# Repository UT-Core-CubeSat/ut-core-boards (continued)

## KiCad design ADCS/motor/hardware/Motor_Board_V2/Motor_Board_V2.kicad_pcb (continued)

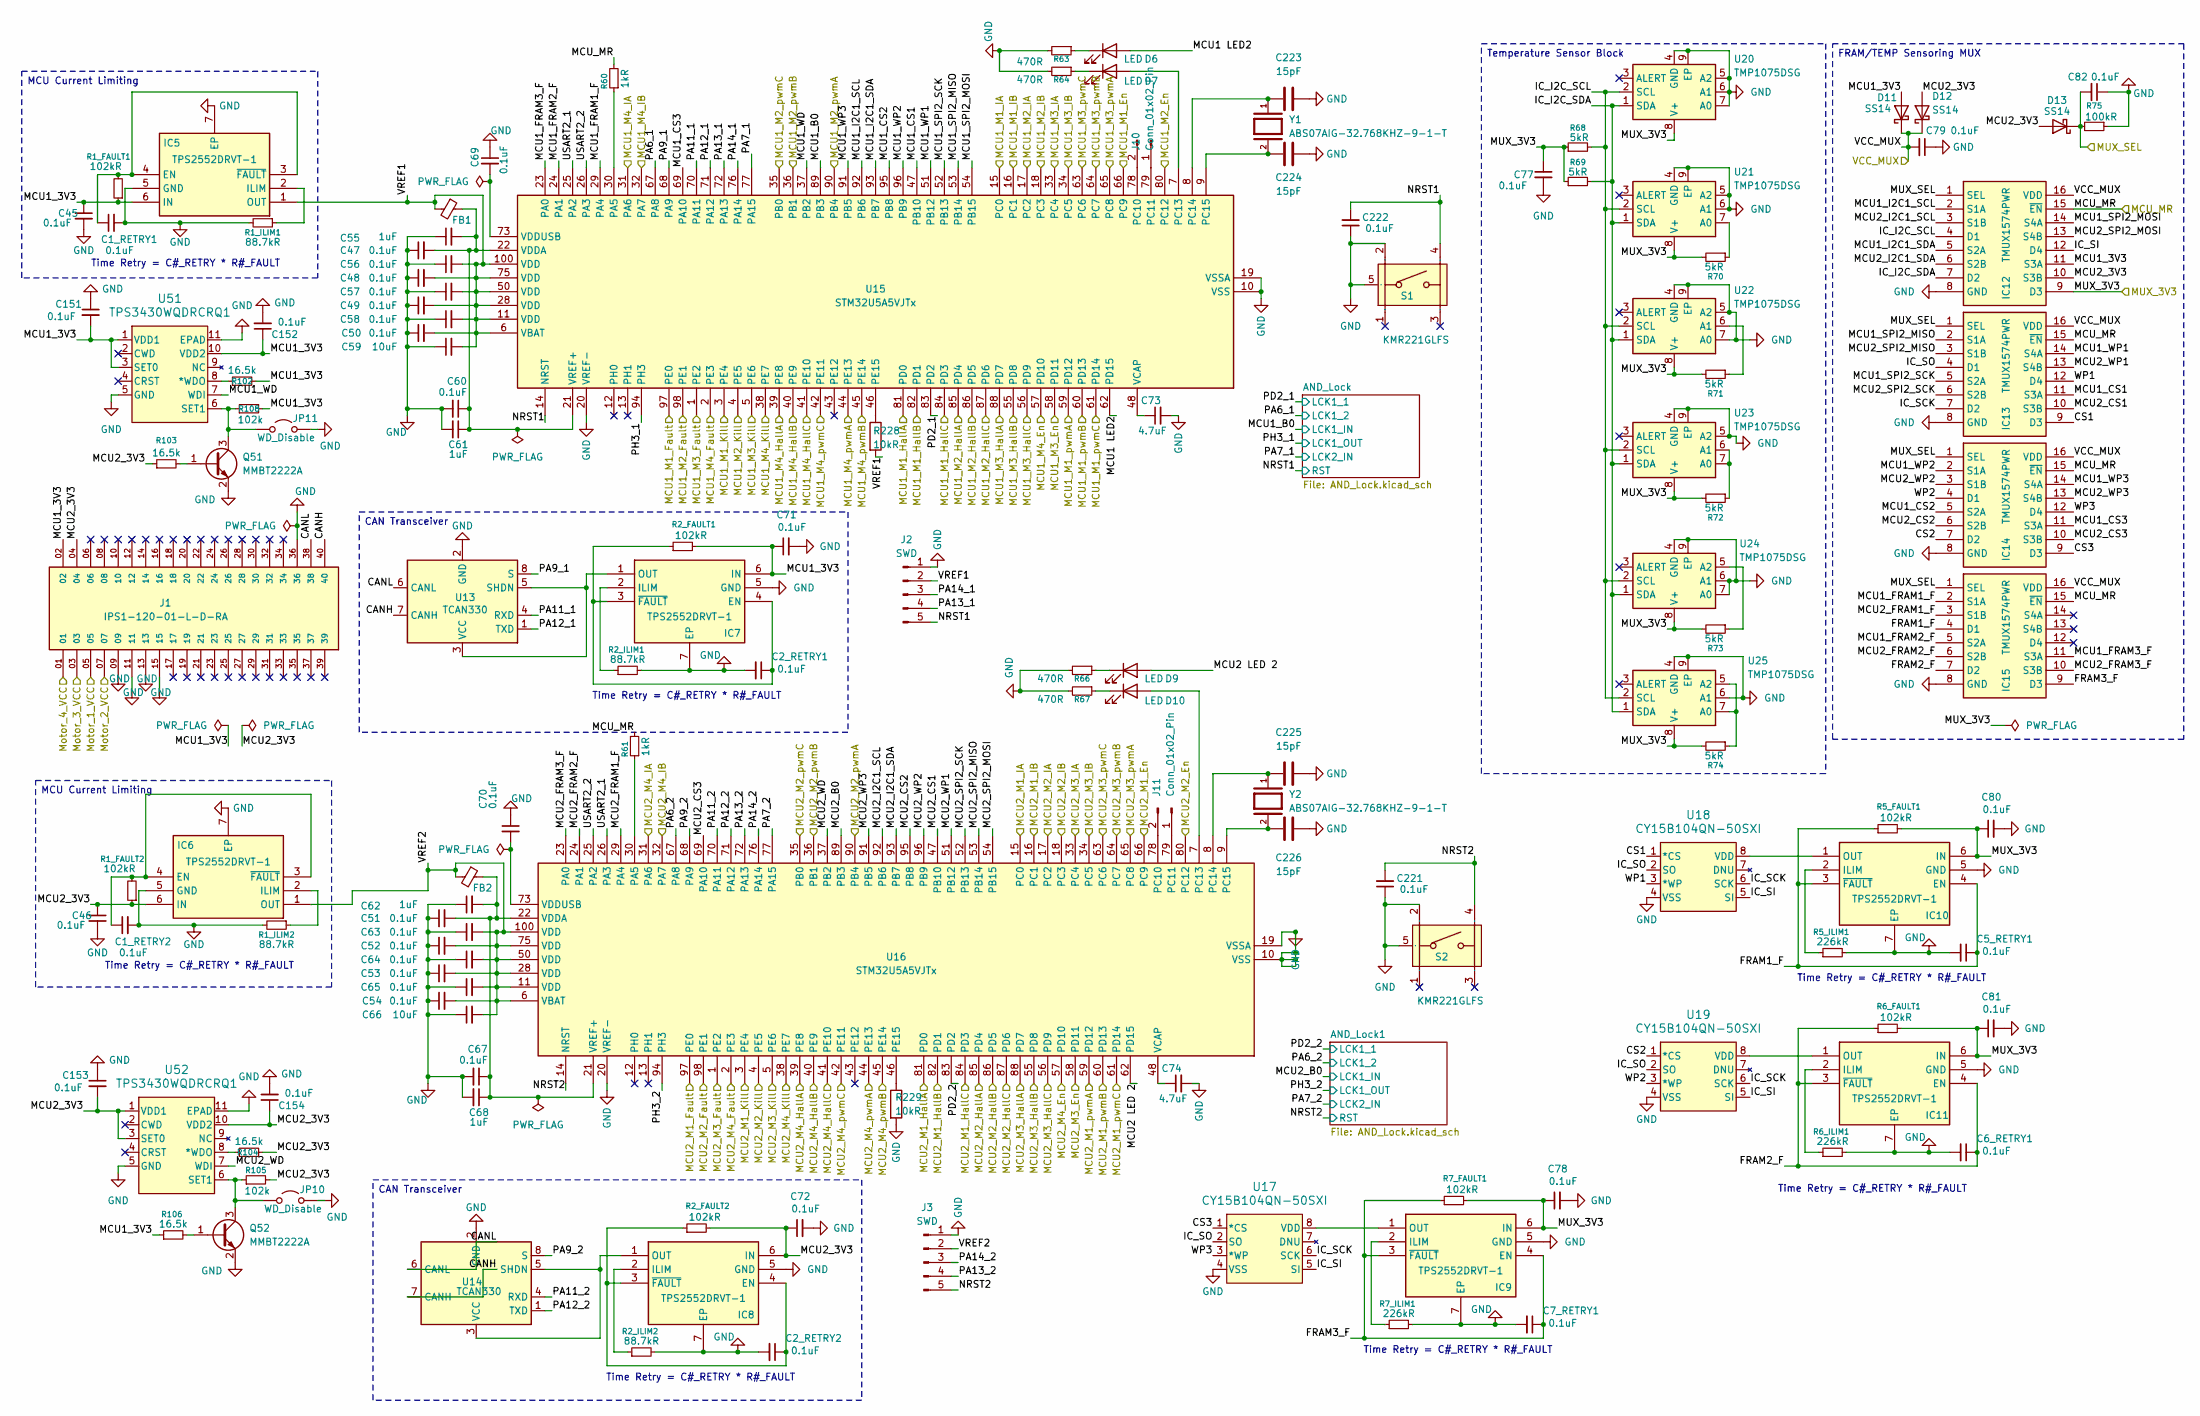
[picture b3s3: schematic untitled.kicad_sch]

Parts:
C1_RETRY1, C1_RETRY2, C2_RETRY1, C2_RETRY2, C5_RETRY1, C6_RETRY1, C7_RETRY1, C45, C46, C47, C48, C49, C50, C51, C52, C53, C54, C56, C57, C58, C63, C64, C65, C69, C70, C71, C72, C77, C78, C79, C80, C81, C82, C151, C152, C153, C154, C221, C222: 0.1uF; C_0603_1608Metric_Pad1.08x0.95mm_HandSolder
C55, C62: 1uF; C_0603_1608Metric_Pad1.08x0.95mm_HandSolder
C59, C66: 10uF; C_0603_1608Metric_Pad1.08x0.95mm_HandSolder
C60, C67: 0.1uF; C_0805_2012Metric_Pad1.18x1.45mm_HandSolder
C61, C68: 1uF; C_0805_2012Metric_Pad1.18x1.45mm_HandSolder
C73, C74: 4.7uF; C_0805_2012Metric_Pad1.18x1.45mm_HandSolder
C223, C224, C225, C226: 15pF; C_0603_1608Metric
D6, D7, D9, D10: LED; LED_0201_0603Metric_Pad0.64x0.40mm_HandSolder
D11, D12, D13: SS14; D_SMA
FB1, FB2: FerriteBead_Small; R_0805_2012Metric_Pad1.20x1.40mm_HandSolder
IC5, IC6, IC7, IC8, IC9, IC10, IC11: TPS2552DRVT-1; Mouser Part Number 595-TPS2552DRVT-1
IC12, IC13, IC14, IC15: TMUX1574PWR; Mouser Part Number 595-TMUX1574PWR
J1: IPS1-120-01-L-D-RA
J2, J3: SWD; PinHeader_1x05_P2.54mm_Vertical
J10, J11: Conn_01x02_Pin; PinHeader_1x02_P2.54mm_Vertical
JP10, JP11: WD_Disable; TestPoint_2Pads_Pitch2.54mm_Drill0.8mm
Q51, Q52: MMBT2222A; SOT-23
R1_FAULT1, R1_FAULT2, R2_FAULT1, R2_FAULT2, R5_FAULT1, R6_FAULT1, R7_FAULT1: 102kR; R_0805_2012Metric_Pad1.20x1.40mm_HandSolder
R1_ILIM1, R1_ILIM2, R2_ILIM1, R2_ILIM2: 88.7kR; R_0805_2012Metric_Pad1.20x1.40mm_HandSolder
R5_ILIM1, R6_ILIM1, R7_ILIM1: 226kR; R_0805_2012Metric_Pad1.20x1.40mm_HandSolder
R60, R61: 1kR; R_0805_2012Metric_Pad1.20x1.40mm_HandSolder
R63, R64, R66, R67: 470R; R_0805_2012Metric_Pad1.20x1.40mm_HandSolder
R68, R69, R70, R71, R72, R73, R74: 5kR; R_0603_1608Metric_Pad0.98x0.95mm_HandSolder
R75: 100kR; R_0805_2012Metric_Pad1.20x1.40mm_HandSolder
R102, R103, R104, R106: 16.5k; R_0805_2012Metric_Pad1.20x1.40mm_HandSolder
R105, R108: 102k; R_0805_2012Metric_Pad1.20x1.40mm_HandSolder
R228, R229: 10kR; R_0805_2012Metric
S1, S2: KMR221GLFS; SW_KMR221GLFS; Manufacturer Part KMR221GLFS; LCSC Part Name 4.6*2.8*1.9mm 立贴 轻触开关
U13, U14: TCAN330; SOIC-8_3.9x4.9mm_P1.27mm
U15, U16: STM32U5A5VJTx; LQFP-100_14x14mm_P0.5mm
U17, U18, U19: CY15B104QN-50SXI
U20, U21, U22, U23, U24, U25: TMP1075DSG; WSON-8-1EP_2x2mm_P0.5mm_EP0.9x1.6mm
U51, U52: TPS3430WQDRCRQ1; SON50P300X300X100-11N
Y1, Y2: ABS07AIG-32.768KHZ-9-1-T; XTAL_ABS07AIG-32.768KHZ-9-1-T; PARTREV 6/7/2022

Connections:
/MUX_3V3: C77.1, C78.1, C80.1, C81.1, IC9.6 (IN), IC10.6 (IN), IC11.6 (IN), IC12.9 (D3), R5_FAULT1.2, R6_FAULT1.2, R7_FAULT1.2, R68.1, R69.1, R70.2, R71.2, R72.2, R73.2, R74.2, U20.8 (V+), U21.8 (V+), U22.8 (V+), U23.8 (V+), U24.8 (V+), U25.8 (V+); also elsewhere on the board
/Motor_1_VCC: J1.05; also elsewhere on the board
/Motor_2_VCC: J1.07; also elsewhere on the board
/Motor_3_VCC: J1.03; also elsewhere on the board
/Motor_4_VCC: J1.01; also elsewhere on the board
/mux/MCU block/CANH: J1.40, U13.7 (CANH), U14.7 (CANH)
/mux/MCU block/CANL: J1.38, U13.6 (CANL), U14.6 (CANL)
/mux/MCU block/CS1: IC13.9 (D3), U18.1 (*CS)
/mux/MCU block/CS2: IC14.7 (D2), U19.1 (*CS)
/mux/MCU block/CS3: IC14.9 (D3), U17.1 (*CS)
/mux/MCU block/FRAM1_F: C5_RETRY1.1, IC10.3 (~FAULT), IC10.4 (EN), IC15.4 (D1), R5_FAULT1.1
/mux/MCU block/FRAM2_F: C6_RETRY1.1, IC11.3 (~FAULT), IC11.4 (EN), IC15.7 (D2), R6_FAULT1.1
/mux/MCU block/FRAM3_F: C7_RETRY1.1, IC9.3 (~FAULT), IC9.4 (EN), IC15.9 (D3), R7_FAULT1.1
/mux/MCU block/IC_I2C_SCL: IC12.4 (D1), R68.2, U20.2 (SCL), U21.2 (SCL), U22.2 (SCL), U23.2 (SCL), U24.2 (SCL), U25.2 (SCL)
/mux/MCU block/IC_I2C_SDA: IC12.7 (D2), R69.2, U20.1 (SDA), U21.1 (SDA), U22.1 (SDA), U23.1 (SDA), U24.1 (SDA), U25.1 (SDA)
/mux/MCU block/IC_SCK: IC13.7 (D2), U17.6 (SCK), U18.6 (SCK), U19.6 (SCK)
/mux/MCU block/IC_SI: IC12.12 (D4), U17.5 (SI), U18.5 (SI), U19.5 (SI)
/mux/MCU block/IC_SO: IC13.4 (D1), U17.2 (SO), U18.2 (SO), U19.2 (SO)
/mux/MCU block/MCU1 LED2: D6.2 (A), U15.62 (PD15)
/mux/MCU block/MCU1_3V3: C45.1, C71.1, C151.2, C152.1, D11.2 (A), IC5.6 (IN), IC7.6 (IN), IC12.11 (S3A), J1.02, R1_FAULT1.1, R2_FAULT1.2, R102.2, R106.1, R108.2, U51.1 (VDD1), U51.3 (SET0), U51.10 (VDD2); also elsewhere on the board
/mux/MCU block/MCU1_B0: U15.89 (PB3); also elsewhere on the board
/mux/MCU block/MCU1_CS1: IC13.11 (S3A), U15.47 (PB10)
/mux/MCU block/MCU1_CS2: IC14.5 (S2A), U15.95 (PB8)
/mux/MCU block/MCU1_CS3: IC14.11 (S3A), U15.69 (PA10)
/mux/MCU block/MCU1_FRAM1_F: IC15.2 (S1A), U15.29 (PA4)
/mux/MCU block/MCU1_FRAM2_F: IC15.5 (S2A), U15.24 (PA1)
/mux/MCU block/MCU1_FRAM3_F: IC15.11 (S3A), U15.23 (PA0)
/mux/MCU block/MCU1_I2C1_SCL: IC12.2 (S1A), U15.92 (PB6)
/mux/MCU block/MCU1_I2C1_SDA: IC12.5 (S2A), U15.93 (PB7)
/mux/MCU block/MCU1_M1_En: U15.66 (PC9); also elsewhere on the board
/mux/MCU block/MCU1_M1_Fault: U15.97 (PE0); also elsewhere on the board
/mux/MCU block/MCU1_M1_HallA: U15.81 (PD0); also elsewhere on the board
/mux/MCU block/MCU1_M1_HallB: U15.82 (PD1); also elsewhere on the board
/mux/MCU block/MCU1_M1_HallC: U15.84 (PD3); also elsewhere on the board
/mux/MCU block/MCU1_M1_IA: U15.15 (PC0); also elsewhere on the board
/mux/MCU block/MCU1_M1_IB: U15.16 (PC1); also elsewhere on the board
/mux/MCU block/MCU1_M1_Kill: U15.3 (PE4); also elsewhere on the board
/mux/MCU block/MCU1_M1_pwmA: U15.59 (PD12); also elsewhere on the board
/mux/MCU block/MCU1_M1_pwmB: U15.60 (PD13); also elsewhere on the board
/mux/MCU block/MCU1_M1_pwmC: U15.61 (PD14); also elsewhere on the board
/mux/MCU block/MCU1_M2_En: U15.80 (PC12); also elsewhere on the board
/mux/MCU block/MCU1_M2_Fault: U15.98 (PE1); also elsewhere on the board
/mux/MCU block/MCU1_M2_HallA: U15.85 (PD4); also elsewhere on the board
/mux/MCU block/MCU1_M2_HallB: U15.86 (PD5); also elsewhere on the board
/mux/MCU block/MCU1_M2_HallC: U15.87 (PD6); also elsewhere on the board
/mux/MCU block/MCU1_M2_IA: U15.17 (PC2); also elsewhere on the board
/mux/MCU block/MCU1_M2_IB: U15.18 (PC3); also elsewhere on the board
/mux/MCU block/MCU1_M2_Kill: U15.4 (PE5); also elsewhere on the board
/mux/MCU block/MCU1_M2_pwmA: U15.90 (PB4); also elsewhere on the board
/mux/MCU block/MCU1_M2_pwmB: U15.36 (PB1); also elsewhere on the board
/mux/MCU block/MCU1_M2_pwmC: U15.35 (PB0); also elsewhere on the board
/mux/MCU block/MCU1_M3_En: U15.58 (PD11); also elsewhere on the board
/mux/MCU block/MCU1_M3_Fault: U15.1 (PE2); also elsewhere on the board
/mux/MCU block/MCU1_M3_HallA: U15.88 (PD7); also elsewhere on the board
/mux/MCU block/MCU1_M3_HallB: U15.55 (PD8); also elsewhere on the board
/mux/MCU block/MCU1_M3_HallC: U15.56 (PD9); also elsewhere on the board
/mux/MCU block/MCU1_M3_IA: U15.33 (PC4); also elsewhere on the board
/mux/MCU block/MCU1_M3_IB: U15.34 (PC5); also elsewhere on the board
/mux/MCU block/MCU1_M3_Kill: U15.5 (PE6); also elsewhere on the board
/mux/MCU block/MCU1_M3_pwmA: U15.65 (PC8); also elsewhere on the board
/mux/MCU block/MCU1_M3_pwmB: U15.64 (PC7); also elsewhere on the board
/mux/MCU block/MCU1_M3_pwmC: U15.63 (PC6); also elsewhere on the board
/mux/MCU block/MCU1_M4_En: U15.57 (PD10); also elsewhere on the board
/mux/MCU block/MCU1_M4_Fault: U15.2 (PE3); also elsewhere on the board
/mux/MCU block/MCU1_M4_HallA: U15.39 (PE8); also elsewhere on the board
/mux/MCU block/MCU1_M4_HallB: U15.40 (PE9); also elsewhere on the board
/mux/MCU block/MCU1_M4_HallC: U15.41 (PE10); also elsewhere on the board
/mux/MCU block/MCU1_M4_IA: U15.31 (PA6); also elsewhere on the board
/mux/MCU block/MCU1_M4_IB: U15.32 (PA7); also elsewhere on the board
/mux/MCU block/MCU1_M4_Kill: U15.38 (PE7); also elsewhere on the board
/mux/MCU block/MCU1_M4_pwmA: U15.44 (PE13); also elsewhere on the board
/mux/MCU block/MCU1_M4_pwmB: U15.45 (PE14); also elsewhere on the board
/mux/MCU block/MCU1_M4_pwmC: U15.42 (PE11); also elsewhere on the board
/mux/MCU block/MCU1_SPI2_MISO: IC13.2 (S1A), U15.53 (PB14)
/mux/MCU block/MCU1_SPI2_MOSI: IC12.14 (S4A), U15.54 (PB15)
/mux/MCU block/MCU1_SPI2_SCK: IC13.5 (S2A), U15.52 (PB13)
/mux/MCU block/MCU1_WD: U15.37 (PB2), U51.7 (WDI)
/mux/MCU block/MCU1_WP1: IC13.14 (S4A), U15.51 (PB12)
/mux/MCU block/MCU1_WP2: IC14.2 (S1A), U15.96 (PB9)
/mux/MCU block/MCU1_WP3: IC14.14 (S4A), U15.91 (PB5)
/mux/MCU block/MCU2 LED 2: D9.2 (A), U16.62 (PD15)
/mux/MCU block/MCU2_3V3: C46.1, C72.1, C153.2, C154.1, D12.2 (A), D13.2 (A), IC6.6 (IN), IC8.6 (IN), IC12.10 (S3B), J1.04, R1_FAULT2.1, R2_FAULT2.2, R103.1, R104.2, R105.2, U52.1 (VDD1), U52.3 (SET0), U52.10 (VDD2); also elsewhere on the board
/mux/MCU block/MCU2_B0: U16.89 (PB3); also elsewhere on the board
/mux/MCU block/MCU2_CS1: IC13.10 (S3B), U16.47 (PB10)
/mux/MCU block/MCU2_CS2: IC14.6 (S2B), U16.95 (PB8)
/mux/MCU block/MCU2_CS3: IC14.10 (S3B), U16.69 (PA10)
/mux/MCU block/MCU2_FRAM1_F: IC15.3 (S1B), U16.29 (PA4)
/mux/MCU block/MCU2_FRAM2_F: IC15.6 (S2B), U16.24 (PA1)
/mux/MCU block/MCU2_FRAM3_F: IC15.10 (S3B), U16.23 (PA0)
/mux/MCU block/MCU2_I2C1_SCL: IC12.3 (S1B), U16.92 (PB6)
/mux/MCU block/MCU2_I2C1_SDA: IC12.6 (S2B), U16.93 (PB7)
/mux/MCU block/MCU2_M1_En: U16.66 (PC9); also elsewhere on the board
/mux/MCU block/MCU2_M1_Fault: U16.97 (PE0); also elsewhere on the board
/mux/MCU block/MCU2_M1_HallA: U16.81 (PD0); also elsewhere on the board
/mux/MCU block/MCU2_M1_HallB: U16.82 (PD1); also elsewhere on the board
/mux/MCU block/MCU2_M1_HallC: U16.84 (PD3); also elsewhere on the board
/mux/MCU block/MCU2_M1_IA: U16.15 (PC0); also elsewhere on the board
/mux/MCU block/MCU2_M1_IB: U16.16 (PC1); also elsewhere on the board
/mux/MCU block/MCU2_M1_Kill: U16.3 (PE4); also elsewhere on the board
/mux/MCU block/MCU2_M1_pwmA: U16.59 (PD12); also elsewhere on the board
/mux/MCU block/MCU2_M1_pwmB: U16.60 (PD13); also elsewhere on the board
/mux/MCU block/MCU2_M1_pwmC: U16.61 (PD14); also elsewhere on the board
/mux/MCU block/MCU2_M2_En: U16.80 (PC12); also elsewhere on the board
/mux/MCU block/MCU2_M2_Fault: U16.98 (PE1); also elsewhere on the board
/mux/MCU block/MCU2_M2_HallA: U16.85 (PD4); also elsewhere on the board
/mux/MCU block/MCU2_M2_HallB: U16.86 (PD5); also elsewhere on the board
/mux/MCU block/MCU2_M2_HallC: U16.87 (PD6); also elsewhere on the board
/mux/MCU block/MCU2_M2_IA: U16.17 (PC2); also elsewhere on the board
/mux/MCU block/MCU2_M2_IB: U16.18 (PC3); also elsewhere on the board
/mux/MCU block/MCU2_M2_Kill: U16.4 (PE5); also elsewhere on the board
/mux/MCU block/MCU2_M2_pwmA: U16.90 (PB4); also elsewhere on the board
/mux/MCU block/MCU2_M2_pwmB: U16.36 (PB1); also elsewhere on the board
/mux/MCU block/MCU2_M2_pwmC: U16.35 (PB0); also elsewhere on the board
/mux/MCU block/MCU2_M3_En: U16.58 (PD11); also elsewhere on the board
/mux/MCU block/MCU2_M3_Fault: U16.1 (PE2); also elsewhere on the board
/mux/MCU block/MCU2_M3_HallA: U16.88 (PD7); also elsewhere on the board
/mux/MCU block/MCU2_M3_HallB: U16.55 (PD8); also elsewhere on the board
/mux/MCU block/MCU2_M3_HallC: U16.56 (PD9); also elsewhere on the board
/mux/MCU block/MCU2_M3_IA: U16.33 (PC4); also elsewhere on the board
/mux/MCU block/MCU2_M3_IB: U16.34 (PC5); also elsewhere on the board
/mux/MCU block/MCU2_M3_Kill: U16.5 (PE6); also elsewhere on the board
/mux/MCU block/MCU2_M3_pwmA: U16.65 (PC8); also elsewhere on the board
/mux/MCU block/MCU2_M3_pwmB: U16.64 (PC7); also elsewhere on the board
/mux/MCU block/MCU2_M3_pwmC: U16.63 (PC6); also elsewhere on the board
/mux/MCU block/MCU2_M4_En: U16.57 (PD10); also elsewhere on the board
/mux/MCU block/MCU2_M4_Fault: U16.2 (PE3); also elsewhere on the board
/mux/MCU block/MCU2_M4_HallA: U16.39 (PE8); also elsewhere on the board
/mux/MCU block/MCU2_M4_HallB: U16.40 (PE9); also elsewhere on the board
/mux/MCU block/MCU2_M4_HallC: U16.41 (PE10); also elsewhere on the board
/mux/MCU block/MCU2_M4_IA: U16.31 (PA6); also elsewhere on the board
/mux/MCU block/MCU2_M4_IB: U16.32 (PA7); also elsewhere on the board
/mux/MCU block/MCU2_M4_Kill: U16.38 (PE7); also elsewhere on the board
/mux/MCU block/MCU2_M4_pwmA: U16.44 (PE13); also elsewhere on the board
/mux/MCU block/MCU2_M4_pwmB: U16.45 (PE14); also elsewhere on the board
/mux/MCU block/MCU2_M4_pwmC: U16.42 (PE11); also elsewhere on the board
/mux/MCU block/MCU2_SPI2_MISO: IC13.3 (S1B), U16.53 (PB14)
/mux/MCU block/MCU2_SPI2_MOSI: IC12.13 (S4B), U16.54 (PB15)
/mux/MCU block/MCU2_SPI2_SCK: IC13.6 (S2B), U16.52 (PB13)
/mux/MCU block/MCU2_WD: U16.37 (PB2), U52.7 (WDI)
/mux/MCU block/MCU2_WP1: IC13.13 (S4B), U16.51 (PB12)
/mux/MCU block/MCU2_WP2: IC14.3 (S1B), U16.96 (PB9)
/mux/MCU block/MCU2_WP3: IC14.13 (S4B), U16.91 (PB5)
/mux/MCU block/PA6_1: U15.67 (PA8); also elsewhere on the board
/mux/MCU block/PA6_2: U16.67 (PA8); also elsewhere on the board
/mux/MCU block/PA7_1: U15.77 (PA15); also elsewhere on the board
/mux/MCU block/PA7_2: U16.77 (PA15); also elsewhere on the board
/mux/MCU block/PA9_1: U13.8 (S), U15.68 (PA9)
/mux/MCU block/PA9_2: U14.8 (S), U16.68 (PA9)
/mux/MCU block/PA11_1: U13.4 (RXD), U15.70 (PA11)
/mux/MCU block/PA11_2: U14.4 (RXD), U16.70 (PA11)
/mux/MCU block/PA12_1: U13.1 (TXD), U15.71 (PA12)
/mux/MCU block/PA12_2: U14.1 (TXD), U16.71 (PA12)
/mux/MCU block/PA13_1: J2.4, U15.72 (PA13)
/mux/MCU block/PA13_2: J3.4, U16.72 (PA13)
/mux/MCU block/PA14_1: J2.3, U15.76 (PA14)
/mux/MCU block/PA14_2: J3.3, U16.76 (PA14)
/mux/MCU block/PD2_1: U15.83 (PD2); also elsewhere on the board
/mux/MCU block/PD2_2: U16.83 (PD2); also elsewhere on the board
/mux/MCU block/PH3_1: U15.94 (PH3); also elsewhere on the board
/mux/MCU block/PH3_2: U16.94 (PH3); also elsewhere on the board
/mux/MCU block/USART2_1: U15.25 (PA2), U16.26 (PA3)
/mux/MCU block/USART2_2: U15.26 (PA3), U16.25 (PA2)
/mux/MCU block/VREF1: C48.2, C49.2, C50.2, C56.2, C57.2, C58.2, C59.2, FB1.2, IC5.1 (OUT), J2.2, R228.2, U15.6 (VBAT), U15.11 (VDD), U15.28 (VDD), U15.50 (VDD), U15.75 (VDD), U15.100 (VDD)
/mux/MCU block/VREF2: C52.2, C53.2, C54.2, C63.2, C64.2, C65.2, C66.2, FB2.2, IC6.1 (OUT), J3.2, U16.6 (VBAT), U16.11 (VDD), U16.28 (VDD), U16.50 (VDD), U16.75 (VDD), U16.100 (VDD)
/mux/MCU block/WP1: IC13.12 (D4), U18.3 (*WP)
/mux/MCU block/WP2: IC14.4 (D1), U19.3 (*WP)
/mux/MCU block/WP3: IC14.12 (D4), U17.3 (*WP)
/mux/MCU_MR: IC12.15 (~EN), IC13.15 (~EN), IC14.15 (~EN), IC15.15 (~EN), R60.2, R61.2; also elsewhere on the board
/mux/MUX_SEL: C82.2, D13.1 (K), IC12.1 (SEL), IC13.1 (SEL), IC14.1 (SEL), IC15.1 (SEL), R75.2; also elsewhere on the board
/mux/VCC_MUX: C79.2, D11.1 (K), D12.1 (K), IC12.16 (VDD), IC13.16 (VDD), IC14.16 (VDD), IC15.16 (VDD); also elsewhere on the board
unnamed: D6.1 (K), R63.1
unnamed: D7.2 (A), U15.7 (PC13)
unnamed: D7.1 (K), R64.1
unnamed: D9.1 (K), R66.1
unnamed: D10.2 (A), U16.7 (PC13)
unnamed: D10.1 (K), R67.1
unnamed: C1_RETRY1.1, IC5.3 (~FAULT), IC5.4 (EN), R1_FAULT1.2
unnamed: IC5.2 (ILIM), R1_ILIM1.1
unnamed: C1_RETRY2.1, IC6.3 (~FAULT), IC6.4 (EN), R1_FAULT2.2
unnamed: IC6.2 (ILIM), R1_ILIM2.1
unnamed: C2_RETRY1.1, IC7.3 (~FAULT), IC7.4 (EN), R2_FAULT1.1
unnamed: IC7.2 (ILIM), R2_ILIM1.1
unnamed: IC7.1 (OUT), U13.3 (VCC), U13.5 (SHDN)
unnamed: C2_RETRY2.1, IC8.3 (~FAULT), IC8.4 (EN), R2_FAULT2.1
unnamed: IC8.2 (ILIM), R2_ILIM2.1
unnamed: IC8.1 (OUT), U14.3 (VCC), U14.5 (SHDN)
unnamed: IC9.2 (ILIM), R7_ILIM1.1
unnamed: IC9.1 (OUT), U17.8 (VDD)
unnamed: IC10.2 (ILIM), R5_ILIM1.1
unnamed: IC10.1 (OUT), U18.8 (VDD)
unnamed: IC11.2 (ILIM), R6_ILIM1.1
unnamed: IC11.1 (OUT), U19.8 (VDD)
unnamed: J10.1, U15.79 (PC11)
unnamed: J10.2, U15.78 (PC10)
unnamed: J11.1, U16.79 (PC11)
unnamed: J11.2, U16.78 (PC10)
unnamed: JP10.1 (A), Q52.3 (C), R105.1, U52.6 (SET1)
unnamed: JP11.1 (A), Q51.3 (C), R108.1, U51.6 (SET1)
unnamed: Q51.1 (B), R103.2
unnamed: Q52.1 (B), R106.2
unnamed: R60.1, U15.30 (PA5)
unnamed: C223.2, U15.8 (PC14), Y1.1
unnamed: C224.1, U15.9 (PC15), Y1.2
unnamed: R228.1, U15.46 (PE15)
unnamed: C73.1, U15.48 (VCAP)
unnamed: C47.2, C55.2, C60.1, C61.1, FB1.1, U15.21 (VREF+), U15.22 (VDDA)
unnamed: C69.2, U15.73 (VDDUSB)
unnamed: R61.1, U16.30 (PA5)
unnamed: C225.2, U16.8 (PC14), Y2.1
unnamed: C226.1, U16.9 (PC15), Y2.2
unnamed: R229.1, U16.46 (PE15)
unnamed: C74.1, U16.48 (VCAP)
unnamed: C51.2, C62.2, C67.1, C68.1, FB2.1, U16.21 (VREF+), U16.22 (VDDA)
unnamed: C70.2, U16.73 (VDDUSB)
unnamed: R70.1, U21.7 (A0)
unnamed: R71.1, U22.6 (A1)
unnamed: R72.1, U23.6 (A1), U23.7 (A0)
unnamed: R73.1, U24.5 (A2)
unnamed: R74.1, U25.5 (A2), U25.7 (A0)
unnamed: R102.1, U51.8 (*WDO)
unnamed: R104.1, U52.8 (*WDO)

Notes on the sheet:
Time Retry = C#_RETRY * R#_FAULT
CAN Transceiver
MCU Current Limiting
Temperature Sensor Block
FRAM/TEMP Sensoring MUX

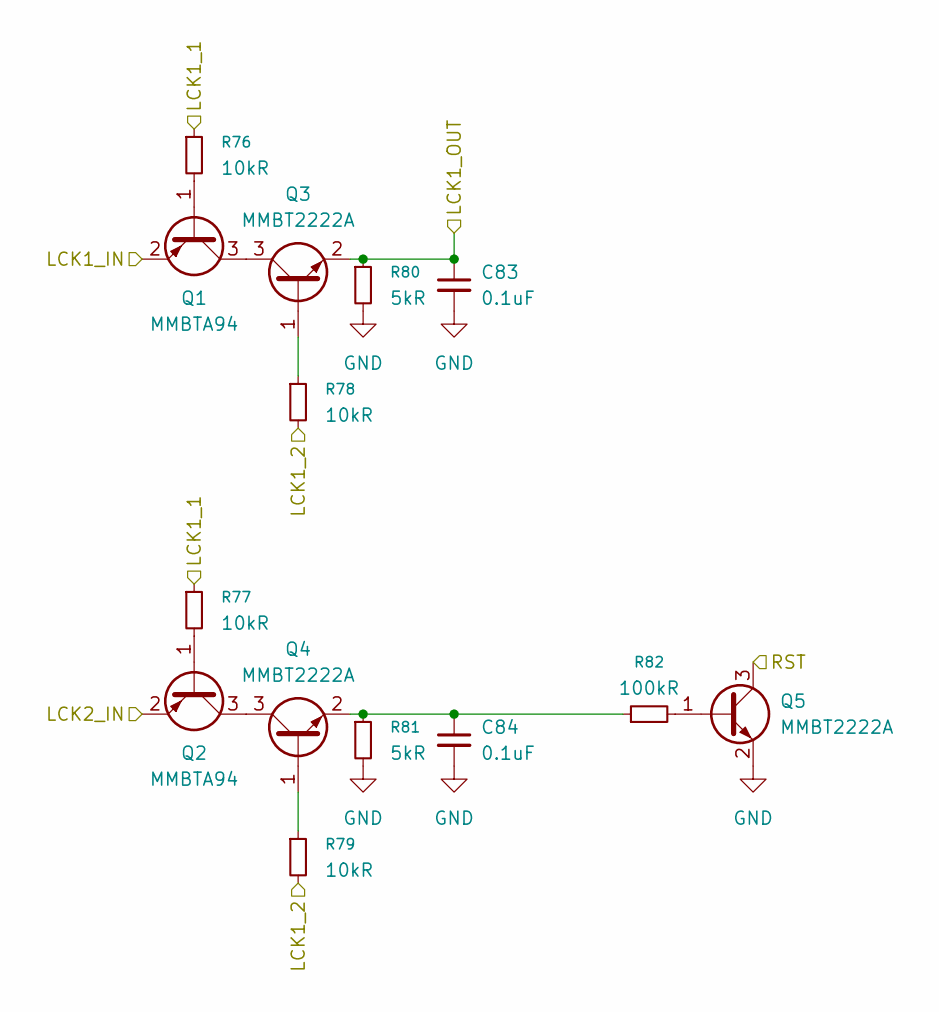
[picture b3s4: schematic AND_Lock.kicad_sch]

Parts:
C83, C84: 0.1uF; C_0603_1608Metric_Pad1.08x0.95mm_HandSolder
Q1, Q2: MMBTA94; SOT-23
Q3, Q4, Q5: MMBT2222A; SOT-23
R76, R77, R78, R79: 10kR; R_0805_2012Metric_Pad1.20x1.40mm_HandSolder
R80, R81: 5kR; R_0805_2012Metric_Pad1.20x1.40mm_HandSolder
R82: 100kR; R_0805_2012Metric_Pad1.20x1.40mm_HandSolder

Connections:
/mux/MCU block/MCU1_B0: Q1.2 (E); also elsewhere on the board
/mux/MCU block/PA6_1: R78.2, R79.2; also elsewhere on the board
/mux/MCU block/PA7_1: Q2.2 (E); also elsewhere on the board
/mux/MCU block/PD2_1: R76.1, R77.1; also elsewhere on the board
/mux/MCU block/PH3_1: C83.1, Q3.2 (E), R80.1; also elsewhere on the board
unnamed: Q1.1 (B), R76.2
unnamed: Q1.3 (C), Q3.3 (C)
unnamed: Q2.1 (B), R77.2
unnamed: Q2.3 (C), Q4.3 (C)
unnamed: Q3.1 (B), R78.1
unnamed: Q4.1 (B), R79.1
unnamed: C84.1, Q4.2 (E), R81.1, R82.1
unnamed: Q5.1 (B), R82.2

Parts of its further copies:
C91, C92: 0.1uF; C_0603_1608Metric_Pad1.08x0.95mm_HandSolder
Q11, Q12: MMBTA94; SOT-23
Q13, Q14, Q15: MMBT2222A; SOT-23
R94, R95, R96, R97: 10kR; R_0805_2012Metric_Pad1.20x1.40mm_HandSolder
R98, R99: 5kR; R_0805_2012Metric_Pad1.20x1.40mm_HandSolder
R100: 100kR; R_0805_2012Metric_Pad1.20x1.40mm_HandSolder

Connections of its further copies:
/mux/MCU block/MCU2_B0: Q11.2 (E); also elsewhere on the board
/mux/MCU block/PA6_2: R96.2, R97.2; also elsewhere on the board
/mux/MCU block/PA7_2: Q12.2 (E); also elsewhere on the board
/mux/MCU block/PD2_2: R94.1, R95.1; also elsewhere on the board
/mux/MCU block/PH3_2: C91.1, Q13.2 (E), R98.1; also elsewhere on the board
unnamed: Q11.1 (B), R94.2
unnamed: Q11.3 (C), Q13.3 (C)
unnamed: Q12.1 (B), R95.2
unnamed: Q12.3 (C), Q14.3 (C)
unnamed: Q13.1 (B), R96.1
unnamed: Q14.1 (B), R97.1
unnamed: C92.1, Q14.2 (E), R99.1, R100.1
unnamed: Q15.1 (B), R100.2

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
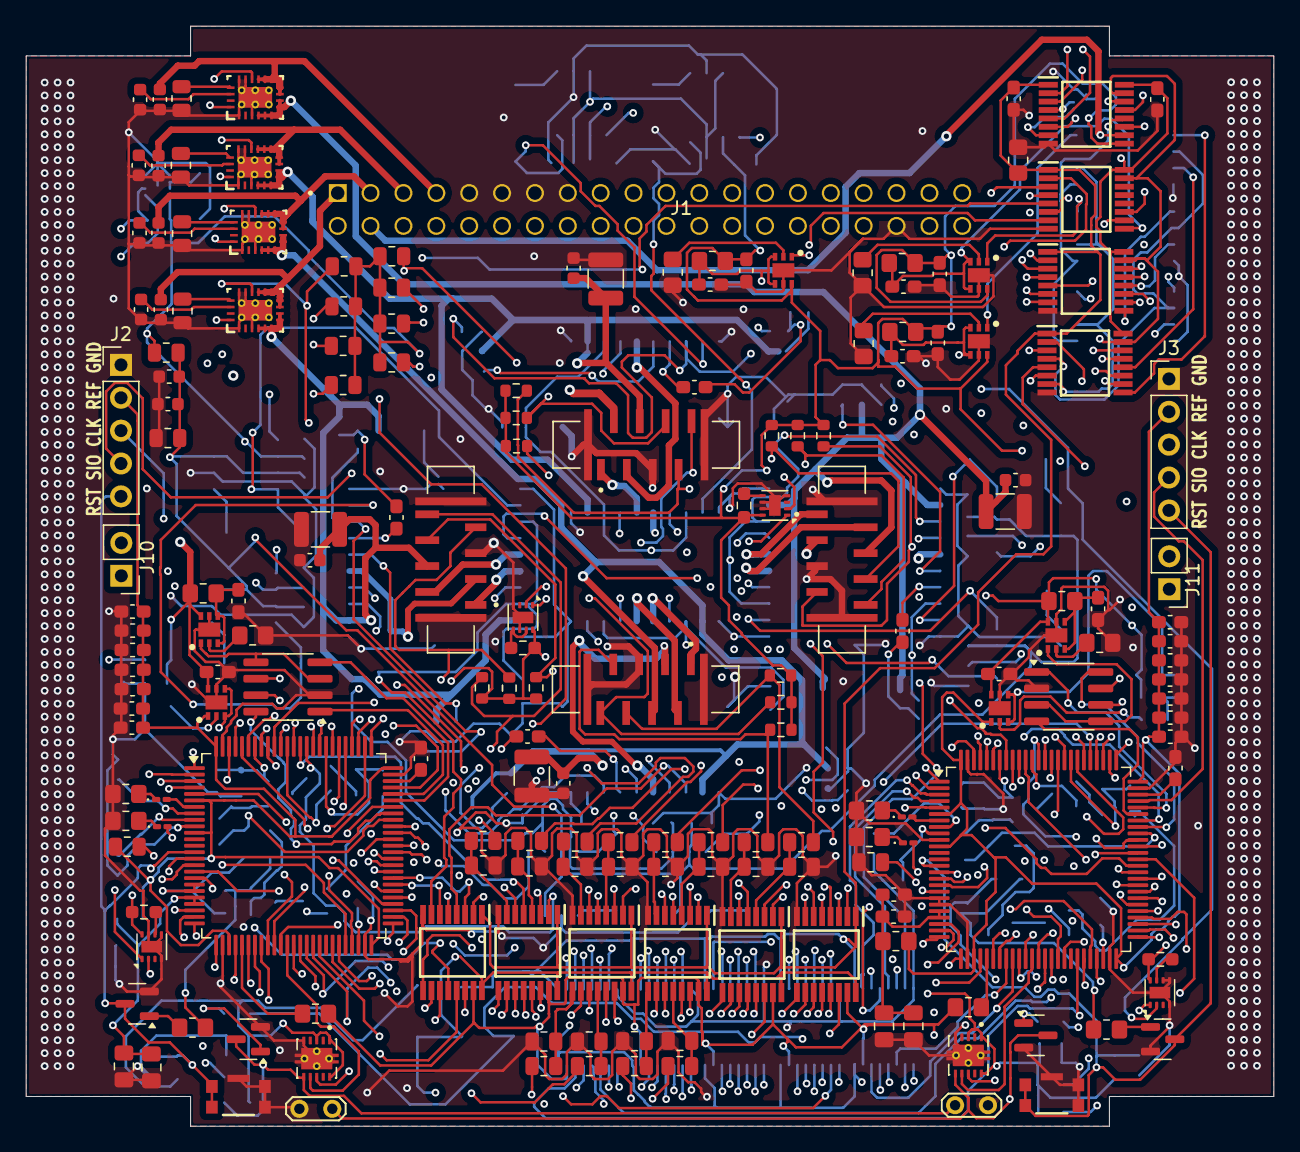
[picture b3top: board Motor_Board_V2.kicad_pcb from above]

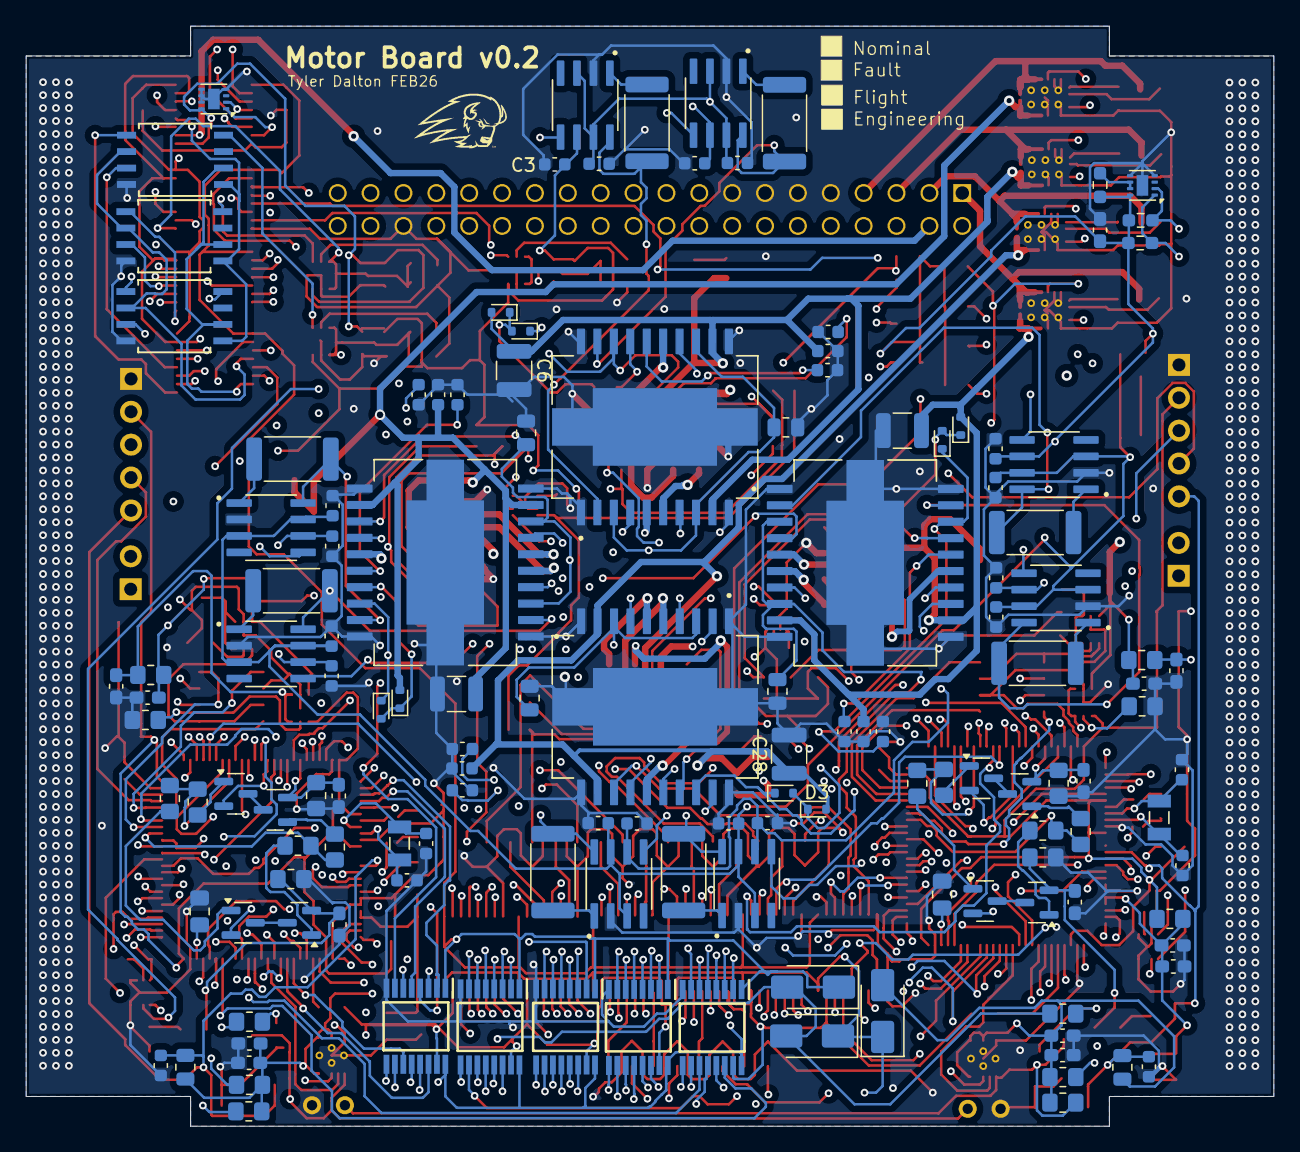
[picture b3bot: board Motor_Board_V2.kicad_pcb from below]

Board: 6 copper layers, 96.4 x 85.0 mm, 322 parts (138 on the bottom side), 353 nets.

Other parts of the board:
R221, R222: 10kR; R_0805_2012Metric

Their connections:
/mux/MCU block/MCU1_3V3: R222.2; also elsewhere on the board
/mux/MCU block/MCU2_3V3: R221.2; also elsewhere on the board
